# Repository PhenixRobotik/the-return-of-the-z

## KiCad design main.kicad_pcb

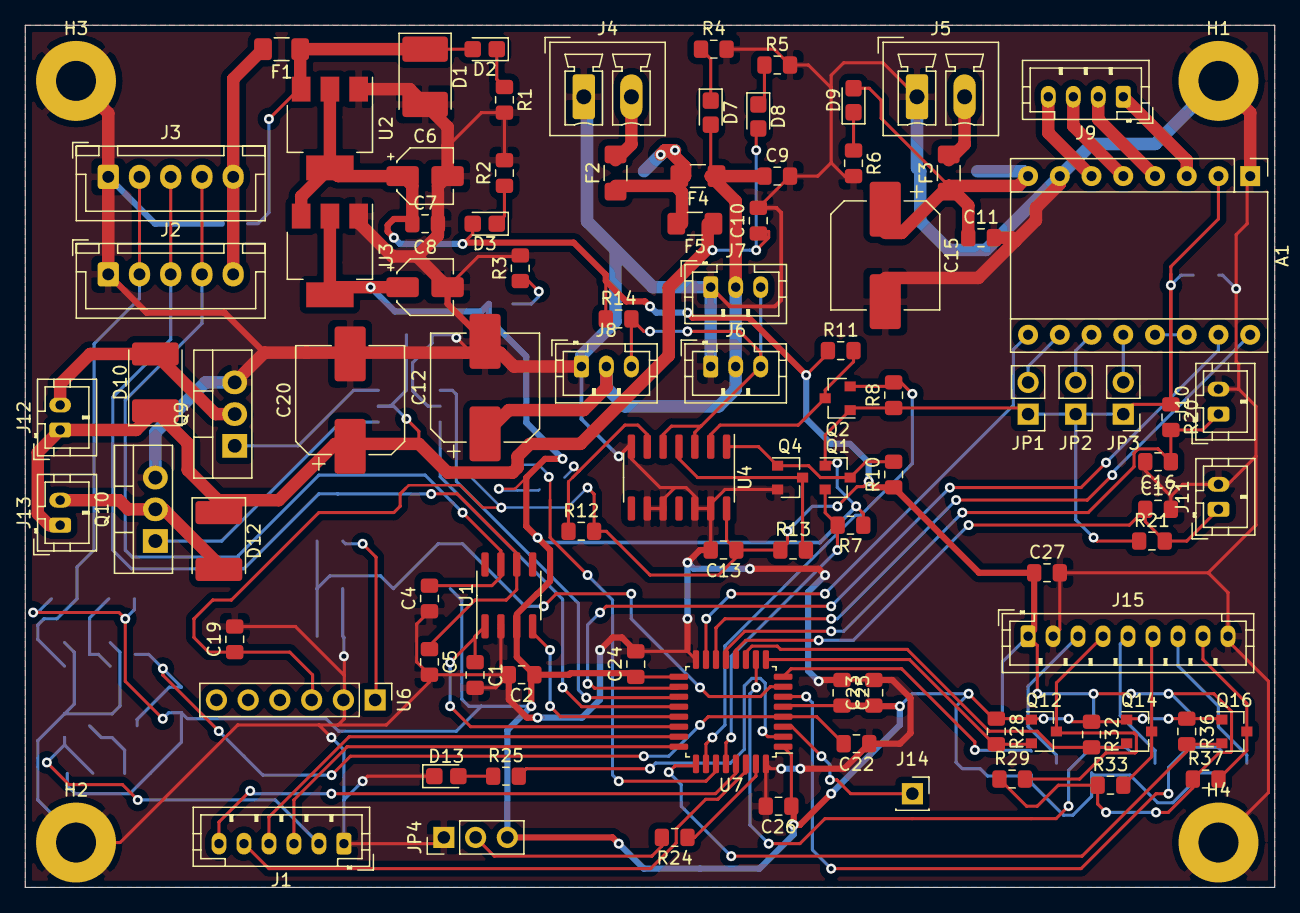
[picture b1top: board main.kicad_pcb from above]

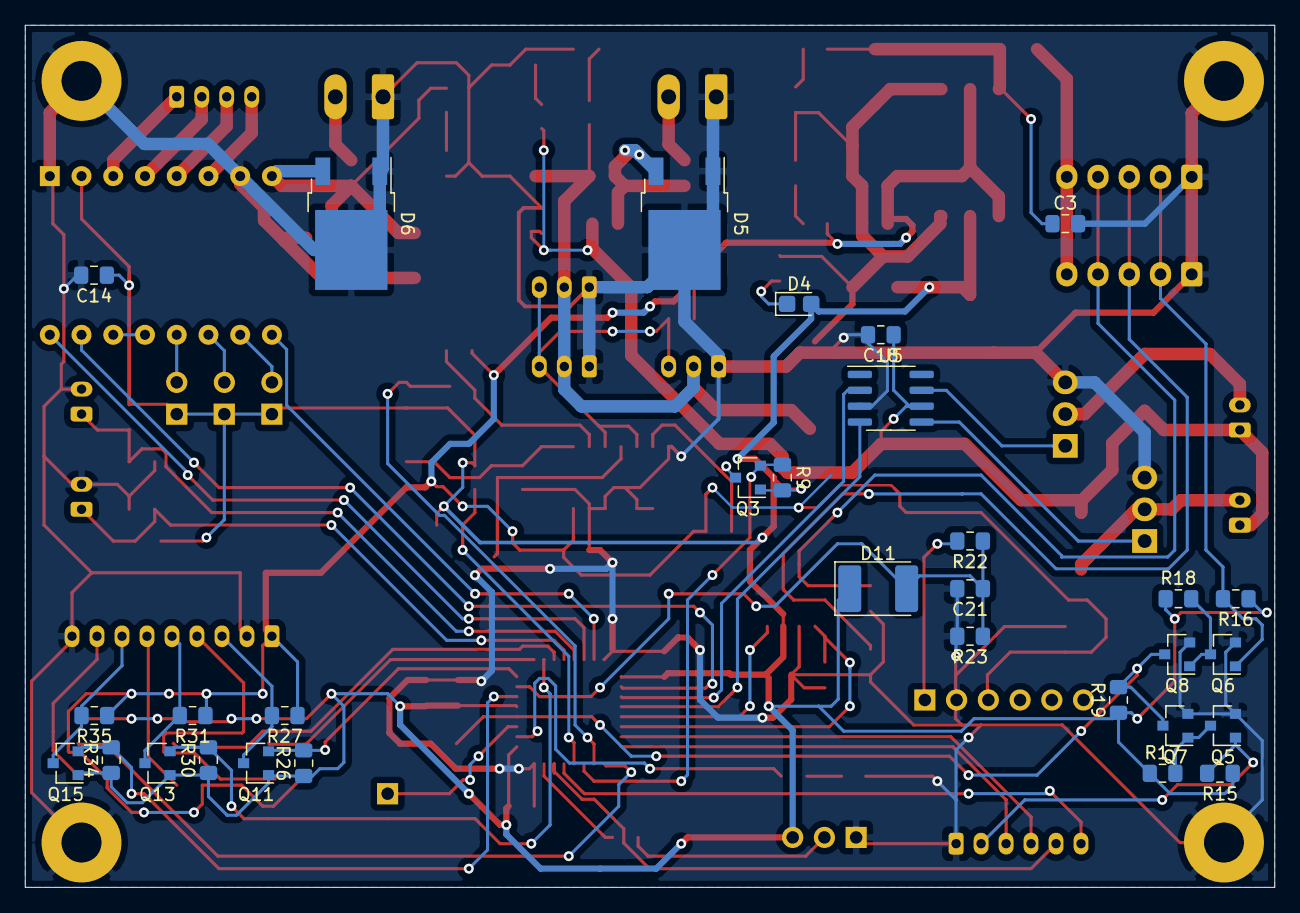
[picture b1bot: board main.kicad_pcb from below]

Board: 2 copper layers, 100.0 x 69.0 mm, 129 parts (31 on the bottom side), 76 nets.

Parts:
A1: Pololu_Breakout_A4988; Pololu_Breakout-16_15.2x20.3mm
C1, C4, C5: 100p; C_0805_2012Metric_Pad1.15x1.40mm_HandSolder
C2: 100nF; C_0805_2012Metric_Pad1.15x1.40mm_HandSolder
C3, C7, C19, C22, C23, C24, C26: 100n; C_0805_2012Metric_Pad1.15x1.40mm_HandSolder
C6, C8: 10u; CP_Elec_4x5.4
C9, C10, C11: C; C_0805_2012Metric_Pad1.15x1.40mm_HandSolder
C12, C15, C20: 100u; CP_Elec_8x10.5
C13, C14, C18, C27: 10n; C_0805_2012Metric_Pad1.15x1.40mm_HandSolder
C16, C17: 1n; C_0805_2012Metric_Pad1.15x1.40mm_HandSolder
C21: 47p; C_0805_2012Metric_Pad1.15x1.40mm_HandSolder
C25: 4.7u; C_0805_2012Metric_Pad1.15x1.40mm_HandSolder
D1: D; D_2114_3652Metric_Castellated
D2, D3, D4, D7, D8, D9, D13: LED_ALT; LED_0805_2012Metric_Castellated
D5, D6: D_Schottky_AAK; TO-252-2
D10, D12: D_ALT; D_2114_3652Metric_Pad1.85x3.75mm_HandSolder
D11: D; D_2114_3652Metric_Pad1.85x3.75mm_HandSolder
F1: Polyfuse 2A; Fuse_1206_3216Metric_Pad1.42x1.75mm_HandSolder
F2, F3: 5A; Fuse_1206_3216Metric_Pad1.42x1.75mm_HandSolder
F4, F5: Fuse; Fuse_1206_3216Metric_Pad1.42x1.75mm_HandSolder
H1, H2, H3, H4: MountingHole_Pad; MountingHole_3.2mm_M3_Pad
J1: Conn_Debug; JST_PH_B6B-PH-K_1x06_P2.00mm_Vertical
J2, J3: CAN_conn; JST_XH_B5B-XH-A_1x05_P2.50mm_Vertical
J4, J5: Conn_Power_In; PhoenixContact_MCV_1,5_2-G-3.81_1x02_P3.81mm_Vertical
J6: AX0; JST_PH_B3B-PH-K_1x03_P2.00mm_Vertical
J7: AX1; JST_PH_B3B-PH-K_1x03_P2.00mm_Vertical
J8: AX2; JST_PH_B3B-PH-K_1x03_P2.00mm_Vertical
J9: stepper; JST_PH_B4B-PH-K_1x04_P2.00mm_Vertical
J10, J11: FC_D_NC; JST_PH_B2B-PH-K_1x02_P2.00mm_Vertical
J12: P0; JST_PH_B2B-PH-K_1x02_P2.00mm_Vertical
J13: V0; JST_PH_B2B-PH-K_1x02_P2.00mm_Vertical
J14: Conn_free; PinSocket_1x01_P2.54mm_Vertical
J15: Conn_01x09; JST_PH_B9B-PH-K_1x09_P2.00mm_Vertical
JP1, JP2, JP3: Jumper_NO_Small; PinHeader_1x02_P2.54mm_Vertical
JP4: JP_Select_Boot; PinHeader_1x03_P2.54mm_Vertical
Q1, Q2, Q3, Q4, Q5, Q6, Q7, Q8, Q11, Q12, Q13, Q14, Q15, Q16: BSS138; SOT-23
Q9, Q10: IRF540N; TO-220-3_Vertical
R1, R2, R3, R4, R5, R6: R_LED; R_0805_2012Metric_Pad1.15x1.40mm_HandSolder
R7, R8, R9, R10, R11, R12, R13, R14, R15, R16, R17, R18, R19, R20, R21, R26, R27, R28, R29, R30, R31, R32, R33, R34, R35, R36, R37: 10k; R_0805_2012Metric_Pad1.15x1.40mm_HandSolder
R22: 20k; R_0805_2012Metric_Pad1.15x1.40mm_HandSolder
R23: 30k; R_0805_2012Metric_Pad1.15x1.40mm_HandSolder
R24: 10kR; R_0805_2012Metric_Pad1.15x1.40mm_HandSolder
R25: 1kR; R_0805_2012Metric_Pad1.15x1.40mm_HandSolder
U1: TCAN332; SOIC-8_3.9x4.9mm_P1.27mm
U2: LD1117S50TR_SOT223; SOT-223-3_TabPin2
U3: LD1117S33TR_SOT223; SOT-223-3_TabPin2
U4: 74LS126; SOIC-14_3.9x8.7mm_P1.27mm
U5: MC34152; SOIC-8_3.9x4.9mm_P1.27mm
U6: MPX5500DP; PinHeader_1x06_P2.54mm_Vertical
U7: STM32F303K8Tx; LQFP-32_7x7mm_P0.8mm

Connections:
+3V3: A1.2, C2.1, C8.1, C14.1, C23.1, C24.1, C25.2, C26.1, D4.2, D11.1, JP1.1, JP2.1, JP3.1, JP4.3, Q1.1, Q2.1, Q3.1, Q11.1, Q12.1, Q13.1, Q14.1, Q15.1, Q16.1, R7.1, R8.1, R9.2, R15.1, R16.1, R17.1, R18.1, R19.1, R20.1, R21.1, R26.1, R28.1, R30.1, R32.1, R34.1, R36.1, U1.3, U3.2, U7.1, U7.5, U7.17
+5V: C6.1, C7.1, C13.1, C19.1, C27.1, D3.2, J15.1, R10.1, R11.1, R12.2, R13.1, R14.1, R27.1, R29.1, R31.1, R33.1, R35.1, R37.1, U2.2, U3.3, U4.14, U6.3
/AX12/DIR: Q1.2, R7.2, U7.28
/AX12/RX: Q3.2, R9.1, U7.27
/AX12/TX: Q2.2, R8.2, U7.26
/CAN/+7V_CAN: F1.2, J2.5, J3.5
/CAN/NRST: J2.2, J3.2, Q6.1, R16.2
/color/LED: Q16.2, R36.2, U7.25
/color/OUT: Q15.2, R34.2, U7.6
/color/S0: Q11.2, R26.2, U7.8
/color/S1: Q12.2, R28.2, U7.9
/color/S2: Q13.2, R30.2, U7.10
/color/S3: Q14.2, R32.2, U7.11
/color/holy_bss138/HV: J15.3, Q11.3, R27.2
/color/sheet5ED3BB89/HV: J15.6, Q14.3, R33.2
/color/sheet5ED3C45C/HV: J15.7, Q15.3, R35.2
/color/sheet5ED3CCBC/HV: J15.8, Q16.3, R37.2
/color/sheet5ED3673B/HV: J15.4, Q12.3, R29.2
/color/sheet5ED37644/HV: J15.5, Q13.3, R31.2
/f3/ADC1_IN2: C21.1, D11.2, R22.1, R23.1, U7.7
/f3/CAN_RX: U1.4, U7.21
/f3/CAN_TX: C1.1, U1.1, U7.22
/f3/FC_D: C16.1, J10.1, R20.2, U7.13
/f3/FC_T: C17.1, J11.1, R21.2, U7.12
/f3/RX_1: J1.5, U7.30
/f3/TCK: J1.3, U7.24
/f3/TIM1_CH3: U5.4, U7.20
/f3/TMS: J1.4, U7.23
/f3/TX_1: J1.6, U7.29
/power_regul/AX_POWER: C9.1, C12.1, D7.2, F4.1, J6.2, J7.2, J8.2
/power_regul/PUMP_POWER: C10.1, C18.1, C20.1, D8.2, D10.1, D12.1, F5.1, J12.1, J13.1, U5.6
/power_regul/STEPPER_POWER: A1.8, C11.1, C15.1, D6.3, D9.2, F3.1
/pump/P0: U5.2, U7.19
/reset_logic/Reset_1: J1.2, Q5.1, R15.2
/reset_logic/Reset_MCU: C22.2, Q7.3, Q8.3, R19.2, U7.4
/stepper/DIR: A1.16, U7.14
/stepper/STEP: A1.15, U7.18
/stepper/~ENABLE: A1.9, U7.15
/stepper/~RESET: A1.13, A1.14
GND: A1.1, A1.7, C1.2, C2.2, C3.2, C4.1, C5.2, C6.2, C7.2, C8.2, C9.2, C10.2, C11.2, C12.2, C13.2, C14.2, C15.2, C16.2, C17.2, C18.2, C19.2, C20.2, C21.2, C22.1, C23.2, C24.2, C25.1, C26.2, C27.2, D1.2, D5.1, D5.2, D6.1, D6.2, D13.1, H1.1, H2.1, H3.1, H4.1, J1.1, J2.1, J3.1, J4.1, J5.1, J6.1, J7.1, J8.1, J10.2, J11.2, J15.2, J15.9, JP4.1, Q4.2, Q5.2, Q6.2, Q7.2, Q8.2, Q9.3, Q10.3, R1.2, R2.2, R3.2, R4.2, R5.2, R6.2, R23.2, U1.2, U2.1, U3.1, U4.7, U4.9, U4.10, U4.12, U4.13, U5.3, U6.2, U7.16, U7.32
unnamed: A1.3, J9.1
unnamed: A1.4, J9.2
unnamed: A1.5, J9.3
unnamed: A1.6, J9.4
unnamed: A1.10, JP1.2
unnamed: A1.11, JP2.2
unnamed: A1.12, JP3.2
unnamed: C3.1, D1.1, D2.2, F1.1, U2.3
unnamed: C4.2, J2.4, J3.4, U1.7
unnamed: C5.1, J2.3, J3.3, U1.6
unnamed: D2.1, R1.1
unnamed: D3.1, R2.1
unnamed: D4.1, R3.1
unnamed: D5.3, F2.1, F4.2, F5.2
unnamed: D7.1, R4.1
unnamed: D8.1, R5.1
unnamed: D9.1, R6.1
unnamed: D10.2, J12.2, Q9.2
unnamed: D12.2, J13.2, Q10.2
unnamed: D13.2, R25.1
unnamed: F2.2, J4.2
unnamed: F3.2, J5.2
unnamed: J6.3, J7.3, J8.3, R14.2, U4.3, U4.5
unnamed: J14.1, U7.3
unnamed: JP4.2, R24.2
unnamed: Q1.3, Q4.1, R10.2, U4.1
unnamed: Q2.3, R11.2, U4.2
unnamed: Q3.3, R12.1, U4.6
unnamed: Q4.3, R13.2, U4.4
unnamed: Q5.3, Q7.1, R17.2
unnamed: Q6.3, Q8.1, R18.2
unnamed: Q9.1, U5.7
unnamed: Q10.1, U5.5
unnamed: R22.2, U6.1
unnamed: R24.1, U7.31
unnamed: R25.2, U7.2

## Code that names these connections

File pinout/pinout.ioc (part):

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Mcu.Name=STM32F303K(6-8)Tx
Mcu.Package=LQFP32
Mcu.UserName=STM32F303K8Tx
PA0.Signal=S_TIM2_CH1_ETR
PA1.Mode=IN2-Single-Ended
PA1.Signal=ADC1_IN2
PA10.Signal=S_TIM1_CH3
PA11.Mode=Master
PA11.Signal=CAN_RX
PA12.Mode=Master
PA12.Signal=CAN_TX
PA13.Mode=Serial_Wire
PA13.Signal=SYS_JTMS-SWDIO
PA14.Mode=Serial_Wire
PA14.Signal=SYS_JTCK-SWCLK
PA15.GPIOParameters=GPIO_Label
PA15.GPIO_Label=color_led
PA15.Signal=GPIO_Output
PA2.GPIOParameters=GPIO_Label
PA2.GPIO_Label=S0
PA2.Signal=GPIO_Output
PA3.GPIOParameters=GPIO_Label
PA3.GPIO_Label=S1
PA3.Signal=GPIO_Output
PA4.GPIOParameters=GPIO_Label
PA4.GPIO_Label=S2
PA4.Signal=GPIO_Output
PA5.GPIOParameters=GPIO_Label
PA5.GPIO_Label=S3
PA5.Signal=GPIO_Output
PA6.GPIOParameters=GPIO_Label
PA6.GPIO_Label=FC_T
PA6.Signal=GPIO_Input
PA7.GPIOParameters=GPIO_Label
PA7.GPIO_Label=FC_D
PA7.Signal=GPIO_Input
PA8.Signal=S_TIM1_CH1
PA9.Signal=S_TIM1_CH2
PB0.GPIOParameters=GPIO_Label
PB0.GPIO_Label=stepper_dir
PB0.Signal=GPIO_Output
PB1.GPIOParameters=GPIO_Label
PB1.GPIO_Label=nenable
PB1.Signal=GPIO_Output
PB3.Mode=Asynchronous
PB3.Signal=USART2_TX
PB4.Mode=Asynchronous
PB4.Signal=USART2_RX
PB5.GPIOParameters=GPIO_Label
PB5.GPIO_Label=dir
PB5.Signal=GPIO_Output
PB6.Mode=Asynchronous
PB6.Signal=USART1_TX
PB7.Mode=Asynchronous
PB7.Signal=USART1_RX
PF0\ /\ OSC_IN.GPIOParameters=GPIO_Label
PF0\ /\ OSC_IN.GPIO_Label=led
PF0\ /\ OSC_IN.Signal=GPIO_Output
RCC.HSEPLLFreq_Value=8000000
RCC.HSE_VALUE=8000000
RCC.SYSCLKFreq_VALUE=8000000
board=custom

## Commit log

2020-05-27 adding library
2020-05-27 base with AX12 logic
2020-05-28 stepper and pump added
2020-05-29 full schematics
2020-05-31 only one missing footprint
2020-05-31 begin routing
2020-05-31 first layout
2020-05-31 Commiting submodule changes from superproject
2020-06-01 routing done
2020-06-07 changing pump sensor
2020-06-13 Modif inputs/outputs pins
2020-06-13 bigger fuses
2020-06-14 cap size rectification
